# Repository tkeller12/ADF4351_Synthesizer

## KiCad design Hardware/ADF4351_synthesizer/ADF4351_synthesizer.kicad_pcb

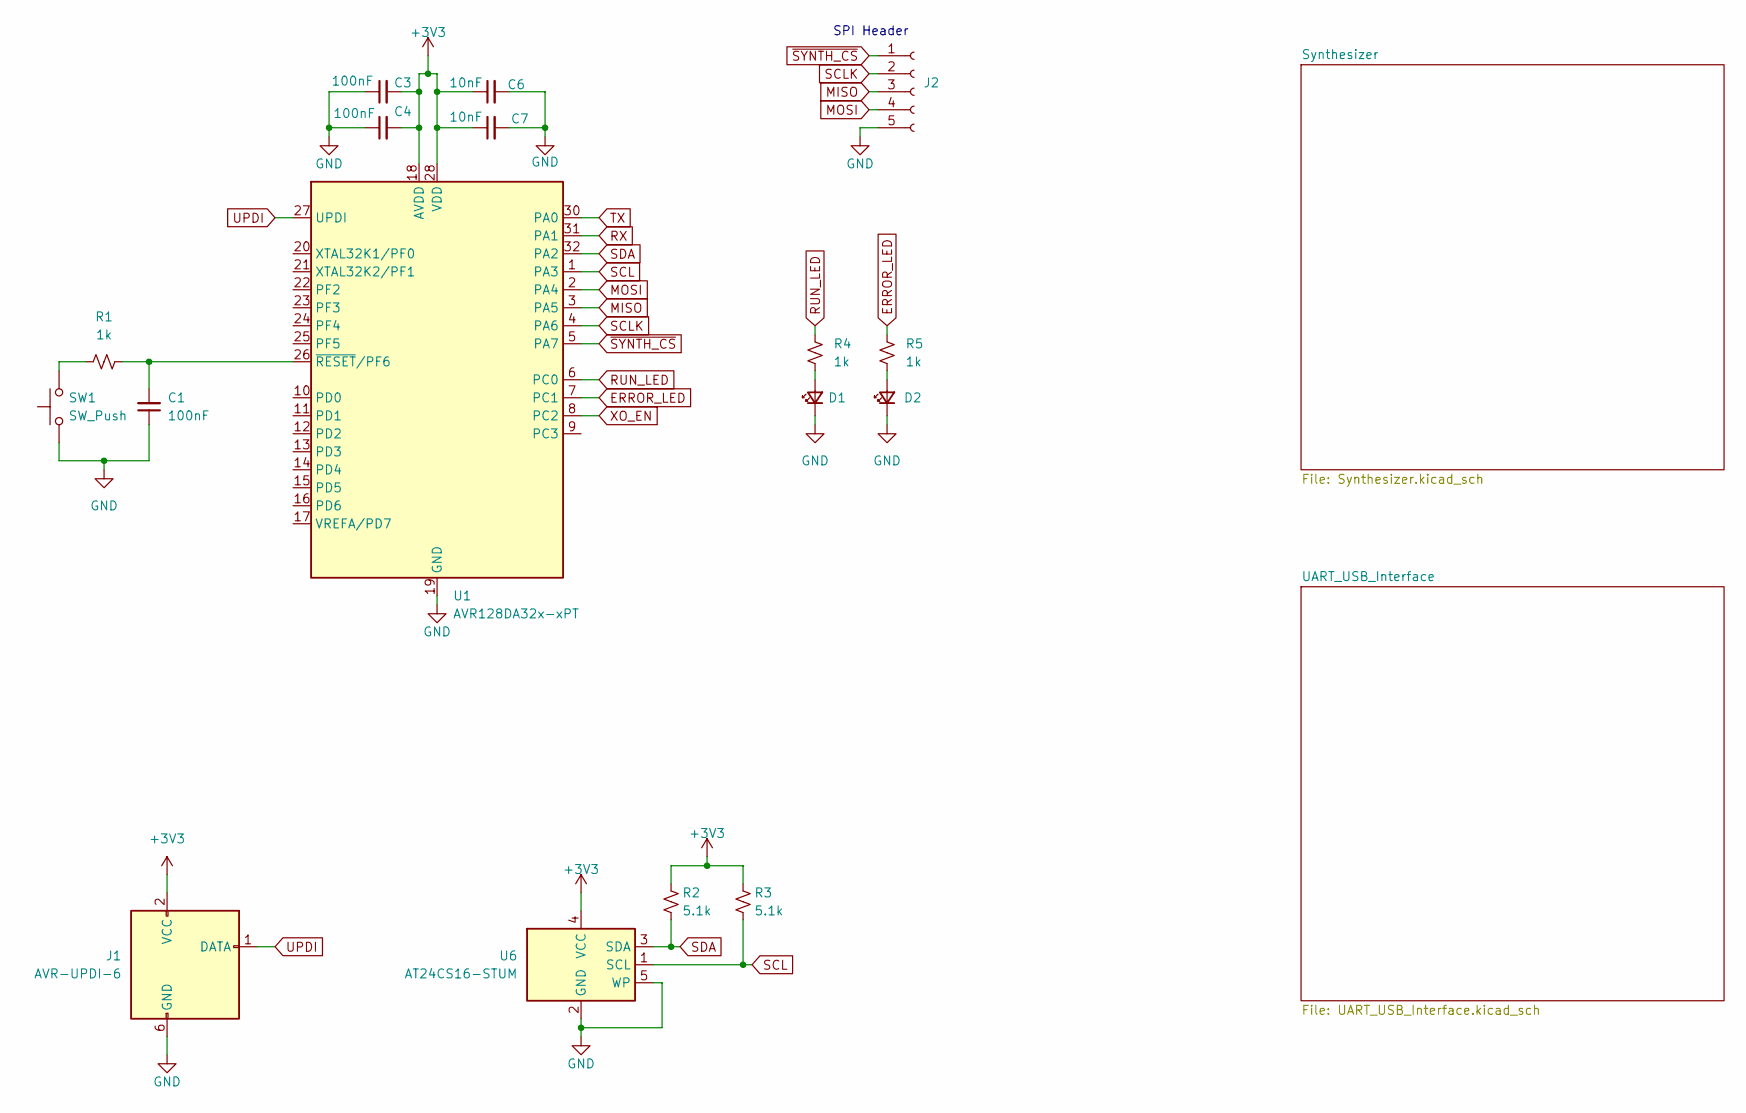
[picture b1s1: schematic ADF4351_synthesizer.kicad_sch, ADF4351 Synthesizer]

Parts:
C1, C3, C4: 100nF; C_0402_1005Metric
C6, C7: 10nF; C_0402_1005Metric
D1: 150080VS75000; LED_0805_2012Metric
D2: 150080SS75000; LED_0805_2012Metric
J1: AVR-UPDI-6; IDC-Header_2x03_P2.54mm_Vertical
J2: Conn_01x05_Socket; PinHeader_1x05_P1.27mm_Vertical
R1, R4, R5: 1k; R_0603_1608Metric
R2, R3: 5.1k; R_0603_1608Metric
SW1: SW_Push; SW_SPST_B3SL-1002P
U1: AVR128DA32x-xPT; TQFP-32_7x7mm_P0.8mm
U6: AT24CS16-STUM; SOT-23-5

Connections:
+3V3: C3.2, C4.2, C6.1, C7.1, J1.2 (VCC), R2.1, R3.1, U1.18 (AVDD), U1.28 (VDD), U6.4 (VCC)
ERROR_LED: R5.1, U1.7 (PC1)
GND: C1.1, C3.1, C4.1, C6.2, C7.2, D1.1 (K), D2.1 (K), J1.6 (GND), J2.5, SW1.1, U1.19 (GND), U1.29 (GND), U6.2 (GND), U6.5 (WP); also elsewhere on the board
MISO: J2.3, U1.3 (PA5)
MOSI: J2.4, U1.2 (PA4); also elsewhere on the board
unnamed: D1.2 (A), R4.2
unnamed: D2.2 (A), R5.2
unnamed: R1.1, SW1.2
unnamed: C1.2, R1.2, U1.26 (~RESET/PF6)
RUN_LED: R4.1, U1.6 (PC0)
RX: U1.31 (PA1); also elsewhere on the board
SCL: R3.2, U1.1 (PA3), U6.1 (SCL)
SCLK: J2.2, U1.4 (PA6); also elsewhere on the board
SDA: R2.2, U1.32 (PA2), U6.3 (SDA)
TX: U1.30 (PA0); also elsewhere on the board
UPDI: J1.1 (DATA), U1.27 (UPDI)
XO_EN: U1.8 (PC2); also elsewhere on the board
~SYNTH_CS: J2.1, U1.5 (PA7); also elsewhere on the board

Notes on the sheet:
SPI Header

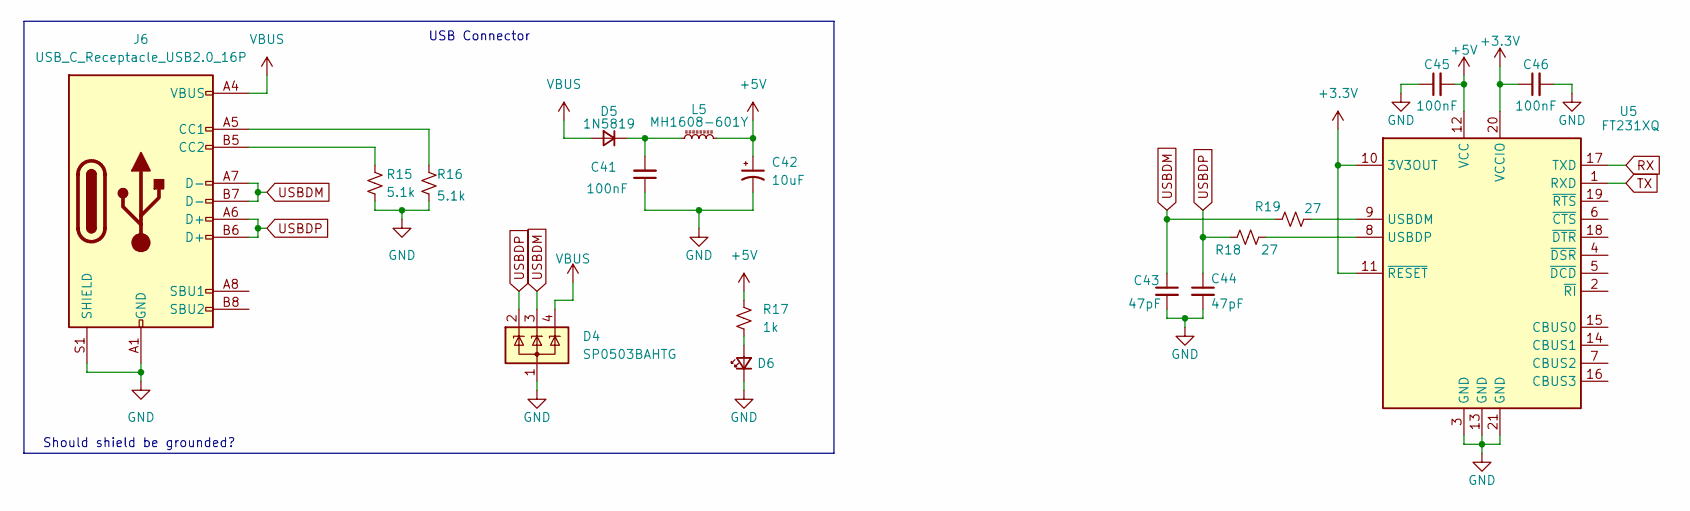
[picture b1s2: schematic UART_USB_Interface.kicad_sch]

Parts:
C41, C45, C46: 100nF; C_0402_1005Metric
C42: 10uF; CP_EIA-3216-18_Kemet-A
C43, C44: 47pF; C_0402_1005Metric
D4: SP0503BAHTG; SOT-143; Digikey F2715CT-ND
D5: 1N5819; D_SOD-123
D6: 150080VS75000; LED_0805_2012Metric
J6: USB_C_Receptacle_USB2.0_16P; USB_C_Receptacle_GCT_USB4085; Digikey 2073-USB4085-GF-ACT-ND
L5: MH1608-601Y; L_0603_1608Metric
R15, R16: 5.1k; R_0603_1608Metric
R17: 1k; R_0603_1608Metric
R18, R19: 27; R_0603_1608Metric
U5: FT231XQ; QFN-20-1EP_4x4mm_P0.5mm_EP2.5x2.5mm

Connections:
+3.3V: C46.1, U5.10 (3V3OUT), U5.11 (~RESET), U5.20 (VCCIO)
+5V: C42.1, C45.2, L5.2, R17.1, U5.12 (VCC); also elsewhere on the board
GND: C41.1, C42.2, C43.2, C44.2, C45.1, C46.2, D4.1 (A), D6.1 (K), J6.A1 (GND), J6.A12 (GND), J6.B1 (GND), J6.B12 (GND), J6.S1 (SHIELD), R15.2, R16.2, U5.3 (GND), U5.13 (GND), U5.21 (GND); also elsewhere on the board
unnamed: C41.2, D5.1 (K), L5.1
unnamed: D6.2 (A), R17.2
unnamed: J6.A5 (CC1), R16.1
unnamed: J6.B5 (CC2), R15.1
unnamed: R19.2, U5.9 (USBDM)
unnamed: R18.2, U5.8 (USBDP)
RX: U5.17 (TXD); also elsewhere on the board
TX: U5.1 (RXD); also elsewhere on the board
USBDM: C43.1, D4.3 (K), J6.A7 (D-), J6.B7 (D-), R19.1
USBDP: C44.1, D4.2 (K), J6.A6 (D+), J6.B6 (D+), R18.1
VBUS: D4.4 (K), D5.2 (A), J6.A4 (VBUS), J6.A9 (VBUS), J6.B4 (VBUS), J6.B9 (VBUS)

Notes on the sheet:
USB Connector
Should shield be grounded?

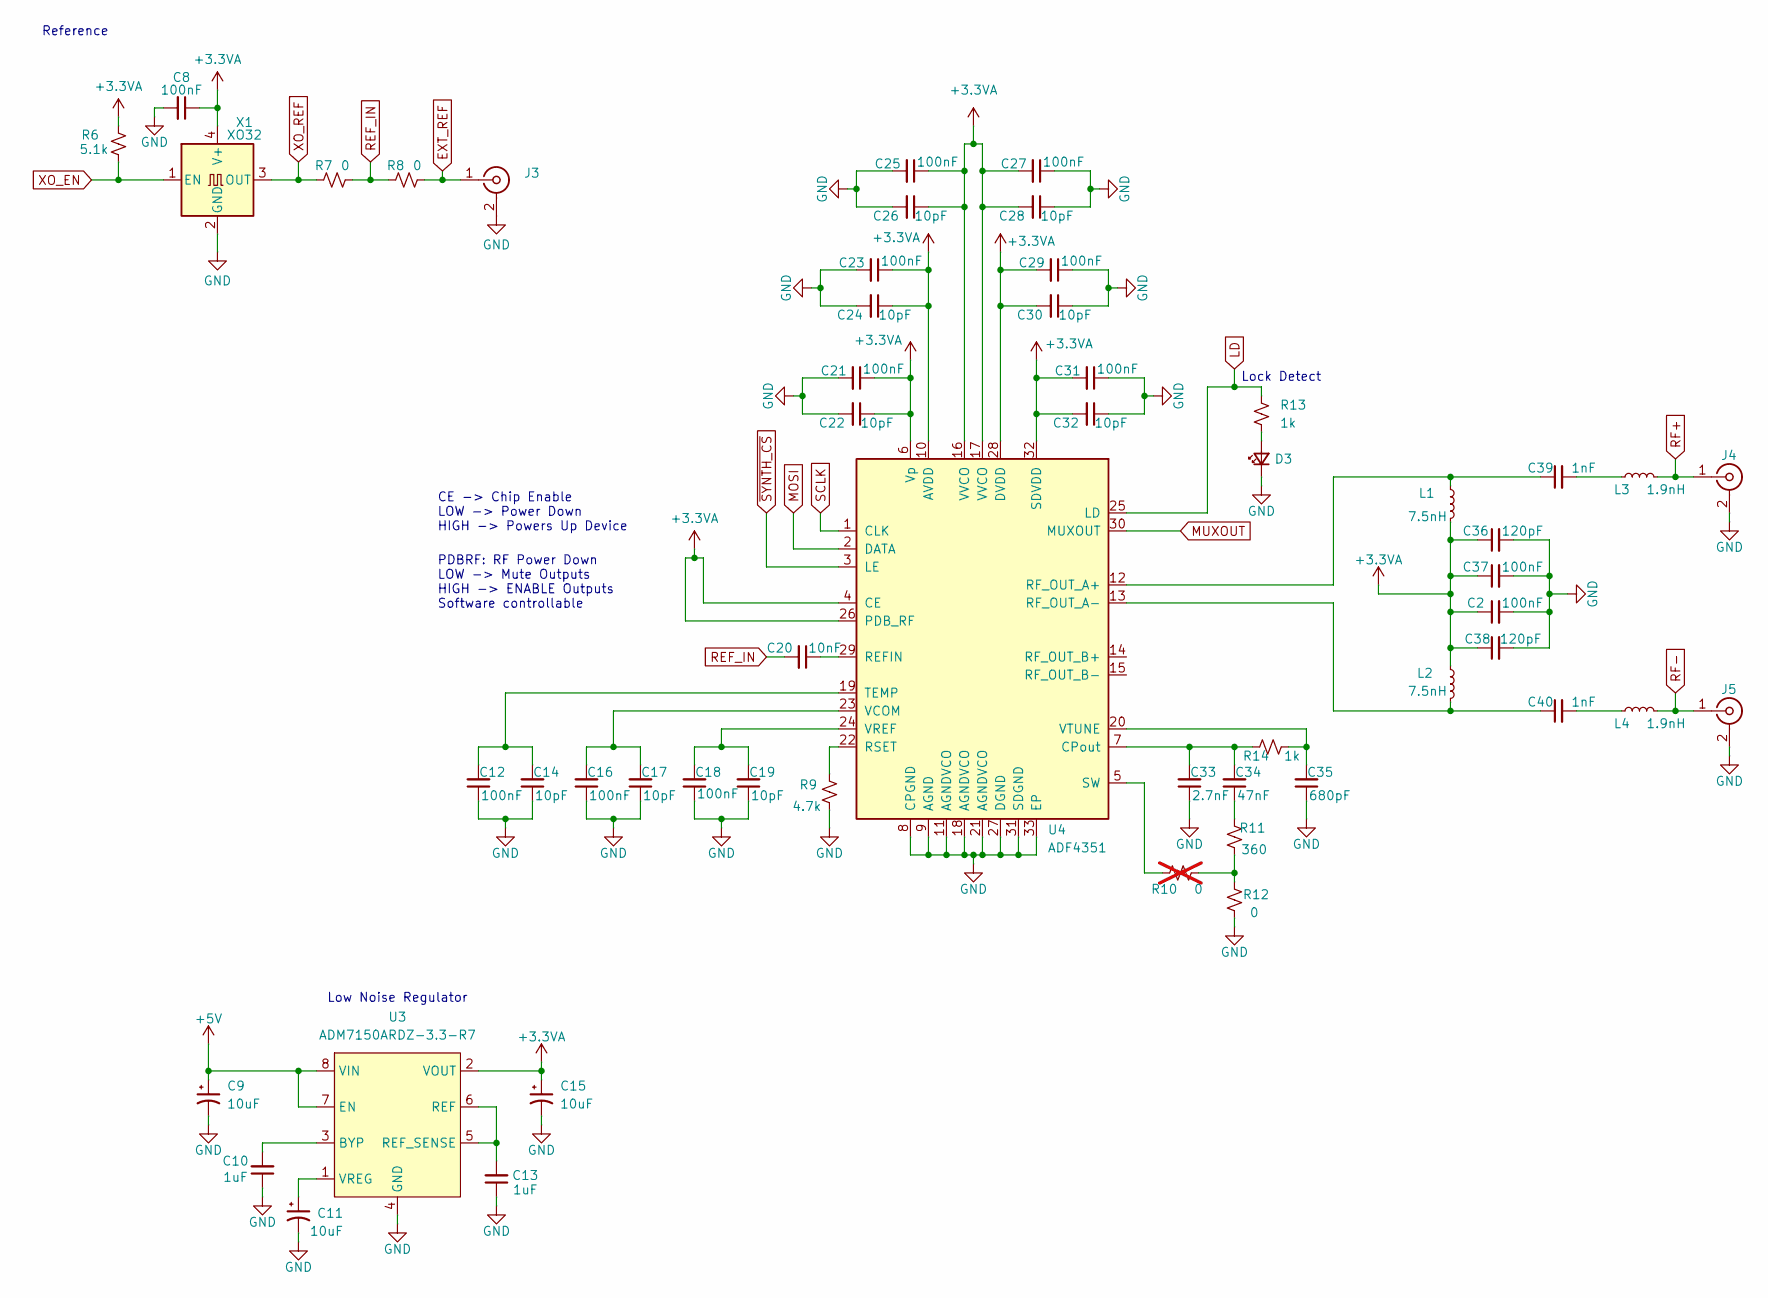
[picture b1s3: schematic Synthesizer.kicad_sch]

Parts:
C2, C8, C12, C16, C18, C21, C23, C25, C27, C29, C31, C37: 100nF; C_0402_1005Metric
C9, C11, C15: 10uF; CP_EIA-3216-18_Kemet-A
C10, C13: 1uF; C_0402_1005Metric
C14, C17, C19, C22, C24, C26, C28, C30, C32: 10pF; C_0402_1005Metric
C20: 10nF; C_0402_1005Metric
C33: 2.7nF; C_0603_1608Metric
C34: 47nF; C_0603_1608Metric
C35: 680pF; C_0603_1608Metric
C36, C38: 120pF; C_0402_1005Metric
C39, C40: 1nF; C_0402_1005Metric
D3: 150080VS75000; LED_0805_2012Metric
J3, J4, J5: SMA-J-P-H-ST-EM1; SMA_Samtec_SMA-J-P-H-ST-EM1_EdgeMount; Digikey SAM8857-ND
L1, L2: 7.5nH; L_0402_1005Metric
L3, L4: 1.9nH; L_0402_1005Metric
R6: 5.1k; R_0603_1608Metric
R7, R8, R12: 0; R_0603_1608Metric
R9: 4.7k; R_0603_1608Metric
R10: 0; R_0603_1608Metric; not fitted
R11: 360; R_0603_1608Metric
R13, R14: 1k; R_0603_1608Metric
U3: ADM7150ARDZ-3.3-R7; SOIC-8-1EP_3.9x4.9mm_P1.27mm_EP2.29x3mm; Digikey 505-ADM7150ARDZ-3.3-R7CT-ND
U4: ADF4351; LFCSP-32-1EP_5x5mm_P0.5mm_EP3.25x3.25mm; Digikey 505-ADF4351BCPZ-RL7CT-ND
X1: XO32; Oscillator_SMD_EuroQuartz_XO32-4Pin_3.2x2.5mm

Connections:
+3.3VA: C2.1, C8.1, C15.1, C21.1, C22.1, C23.1, C24.1, C25.1, C26.1, C27.2, C28.2, C29.2, C30.2, C31.2, C32.2, C36.1, C37.1, C38.1, L1.2, L2.1, R6.1, U3.2 (VOUT), U4.4 (CE), U4.6 (Vp), U4.10 (AVDD), U4.16 (VVCO), U4.17 (VVCO), U4.26 (PDB_RF), U4.28 (DVDD), U4.32 (SDVDD), X1.4 (V+)
+5V: C9.1, U3.7 (EN), U3.8 (VIN); also elsewhere on the board
EXT_REF: J3.1 (In), R8.1
GND: C2.2, C8.2, C9.2, C10.1, C11.2, C12.1, C13.1, C14.1, C15.2, C16.1, C17.1, C18.1, C19.1, C21.2, C22.2, C23.2, C24.2, C25.2, C26.2, C27.1, C28.1, C29.1, C30.1, C31.1, C32.1, C33.1, C35.1, C36.2, C37.2, C38.2, D3.1 (K), J3.2 (Ext), J4.2 (Ext), J5.2 (Ext), R9.2, R12.1, U3.4 (GND), U3.9 (EP), U4.8 (CPGND), U4.9 (AGND), U4.11 (AGNDVCO), U4.18 (AGNDVCO), U4.21 (AGNDVCO), U4.27 (DGND), U4.31 (SDGND), U4.33 (EP), X1.2 (GND); also elsewhere on the board
LD: R13.1, U4.25 (LD)
MOSI: U4.2 (DATA); also elsewhere on the board
MUXOUT: U4.30 (MUXOUT)
unnamed: C34.1, R11.2
unnamed: C39.2, L3.1
unnamed: C40.2, L4.1
unnamed: D3.2 (A), R13.2
unnamed: R10.1, R11.1, R12.2
unnamed: C10.2, U3.3 (BYP)
unnamed: C13.2, U3.5 (REF_SENSE), U3.6 (REF)
unnamed: C11.1, U3.1 (VREG)
unnamed: C33.2, C34.2, R14.1, U4.7 (CPout)
unnamed: C20.1, U4.29 (REFIN)
unnamed: C39.1, L1.1, U4.12 (RF_OUT_A+)
unnamed: C40.1, L2.2, U4.13 (RF_OUT_A-)
unnamed: R9.1, U4.22 (RSET)
unnamed: R10.2, U4.5 (SW)
unnamed: C12.2, C14.2, U4.19 (TEMP)
unnamed: C16.2, C17.2, U4.23 (VCOM)
unnamed: C18.2, C19.2, U4.24 (VREF)
unnamed: C35.2, R14.2, U4.20 (VTUNE)
REF_IN: C20.2, R7.2, R8.2
RF+: J4.1 (In), L3.2
RF-: J5.1 (In), L4.2
SCLK: U4.1 (CLK); also elsewhere on the board
XO_EN: R6.2, X1.1 (EN); also elsewhere on the board
XO_REF: R7.1, X1.3 (OUT)
~SYNTH_CS: U4.3 (LE); also elsewhere on the board

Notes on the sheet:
Reference
CE -> Chip Enable LOW -> Power Down HIGH -> Powers Up Device
Low Noise Regulator
PDBRF: RF Power Down LOW -> Mute Outputs HIGH -> ENABLE Outputs Software controllable
Lock Detect

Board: 4 copper layers, 88 parts (0 on the bottom side), 54 nets, no tracks yet.

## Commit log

2024-11-20 Adding KiCad schematic
2024-11-20 Updating schematic
2024-11-21 Adding low noise regulator to schematic
2024-11-21 Starting to organize PCB Layout
2024-11-22 Updating board
2024-11-23 Working on Board Layout
